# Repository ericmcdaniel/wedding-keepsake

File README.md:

# Wedding Keychain Keepsake

This is the full schematic, design, plans, and source code for the interactive RGB LED keepsake gadget from Eric and Stephie's wedding on Saturday August 15th 2026. These PCBs are attached to a keychain and were distributed to guests as keepsake party favors. The keychain displays a bright grid of LED lights and features simple animations and games.

# Modes

When powered on, the keychain begins in either one of two modes: Animation mode and Game mode. Press and Hold the button for one second to switch between Animation and Game modes.

### Animation Mode

The keychain displays an animation from the selection below. Single-press the button to cycle between the following animations.
* Tunnel
* Swipe
* Rainbow
* American Flag
* Candle

### Game Mode

As of this writing, the keychain only offers one game named *Dodge*. Dodge is a space-themed endless runner arcade survival game. You are piloting a space shuttle, traveling through the solar system. You encouter space debris, and must evade them before they collide into you.

Single-press the button to steer your rocket in the opposite direction to dodge obstacles. Survive as long as you can, even as you accelerate through the debris at progressively faster rates.

# Bill of Materials

* 32 acrylic-diffused RGB LEDs, arranged in an 8x4 matrix.
* ~~A MEMS microphone and op-amp for simple audio sampling (no FFT).~~
  * This idea was included in the design and was manufactured. The idea was to create additional audio-reactive (and interactive) modes like animations for decibel and music analyzers, but development time exceeded my delivery timeline. This will be revisited later in future updates.
* Animations can be cycled and games that can be played using the single tactile push button.
* Controlled by the AVR-based ATtiny1614 manufactured by *Microchip Technology*.
* Powered by a 24mm x 5mm CR2450 coin cell battery.
* On an 80mm x 30mm PCB with a D-hook clasp and snake keychain.
* Placed inside a custom-made sled enclosure with snap-fit sliding lid.

# Design

## 3D Rendering

<p align="center"><i>Front side of the PCB</i></p>

<p align="center"><i>Back side of the PCB</i></p>

## Electrical Schematic

## PCB Layout

<p align="center"><i>Layer 1 of the PCB (signals/components)</i></p>

<p align="center"><i>Layer 2 of the PCB (GND)</i><p>

<p align="center"><i>Layer 3 of the PCB (3V3 copper pour)</i><p>

<p align="center"><i>Layer 4 of the PCB (Additional signals/components)</i><p>

# Details

### Architecture and Engine

This repository was built using the toolkits provided by PlatformIO. It is based on the Arduino framework, though quite minimally. An RTOS is not used, fairly bare metal in terms of architecture. To keep things as efficient as possible, abstractions that Arduino provides like `digitalWrite()` were replaced with direct register manipulations, especially duirng hot execution paths. Most notably it is used during the LED rendering logic, which renders each row sequentially for 50 microseconds, creating a multiplexed effect on the display, as if all the LEDs were on simutaneously. The main reason that the Arduino framework is still used is because of the timers.

Internally, this repo was built on top of the custom game engine used in the [LumenLab](https://github.com/ericmcdaniel/lumenlab), with a handful of adaptations. This includes the platform-level core services, the engine, and general architecture from the LumenLab. This repo implements multiplexing manually, so libraries like FastLED used in the LumenLab could not be used. The keychain runs the main game loop at 60 Hz. Between each frame, the engine multiplexes each row at a frequency of 20 kHz (50 microseconds). Between each row rendering, three shift registers designated to the red, green, and blue channels take in a serial stream of bits to indicate if the respective color's LED should be on. If it's signal LOW, the LED turns on, and if signal HIGH then off. (this is in reverse because the MOSFETS are active HIGH).

Pulse-width modulation (PWM) is needed to dim the three primary colors, allowing for any arbitrary color can be made via blending. This was implemented using [bit-angle modulation (BAM)](https://www.desertember.com/posts/bit-angle-modulation.html) to determine the duty cycle. That was a headache, almost literally, because given large time values, the PWM's duty cycle would be so spread your eyes would noticably see the flicker. The color depth was reduced to 6-bit. The flicker isn't fully removed, but it's significantly better. Brightness and gamma correction was implemented, but disabled because adjustmenets is needed (again, mostly due to the noticable PWM flicker).

### Audio profiling (not implemented)

A MEMS microphone and amplifier was a part of the keychain's goal and is still a part of the design and schematic. The idea was realistic to implement, but was bound by an ambitious timeline, so I had to pause development that for now. The microphone still remains on the PCB since they were already manufactured (center-right). This gives me the opportunity to simply suspend working on the audio-reactive features rather than cancel entirely.

The idea for this keychain was to include audio reactivity, which would complement the already interactive animations. Running a full spectrum analyzer was not possible given the microcontroller selected, power constraints, and technical limitations like the inability to timely perform computationally heavy Fast-Fourier Transformations (FFT). So to be clear, it is too low-powered/low-budget to record conversation. Instead, the device was going to sample decibel levels in real time and display a sound-reactive bar, like the EQ on a stereo system. Another idea I had for the built-in microphone was to make the devices react to the wedding reception music live in real time. Between songs, I could have my computer play a swift, 20+ kHz logic signal at the before every song. This high-frequency chirp wouldn't be heard by humans, but detected by this keychain. It would then decode the message, and play an animation or color theme dynamically, as if it's listening to the music and dancing along.

These were two ideas that have artifacts on the board, but were not implemented.

# Development

### Software

The keychain is programmable using the UPDI protocol, which is the newer version of AVR's ISP and JTAG programming. The UPDI (PA0, pin 10) is exposed on a THT test pad, along with 3V3 and GND. To program the device, you need a $7 module called the UPDI Friend - USB Serial UPDI Programmer from [Adafruit](https://www.adafruit.com/product/5879) or [Digikey](https://www.digikey.com/en/products/detail/adafruit-industries-llc/5879/22596413). Releases are provided every PR and can be flashed directly. I'll write instructions to directly flash the device later (hopefully), and possibly even dockerize it for simplicity. Until then, the easiest way to update is to install the PlatformIO toolkit, compile this repo locally, and flash using the *PlatformIO: Upload (Release)* build script included.

In addition to the UPDI pin, PB2 (pin 7) and PB3 (pin 6) are mapped to TX and RX respectively. Because they were unused, these pins are exposed as SMD test pads. This allows you to probe TX (PB2) to read the serial logs, if you compiled the debug version.

### Hardware

The PCB design files were made using KiCad 9.0.5. The board layout was optimized for the manufacturing capabilities of [PCBWay](https://www.pcbway.com/). Before you start writing me hate mail, know that I'm aware of the issues, such as the lack of ESD protection and reverse polarity protection. Perhaps a future revision can include these, but I have no such plans.

The enclosure was made using FreeCAD 1.1.0. They also suck, but I tried. The models were also exported as .3mf files, and were optimized for immediate FDM printing, particularly the Bambu Labs A1 Combo. Feel free to adjust as needed for your machine. The model includes a sled enclosure which retains the PCB using four friction fit ribs. A lid is attached by sliding it along the guide rails from left to right. A snap-fit latch locks the lid in place, preventing it from falling off. I printed this using Bambu Lab's PLA Basic, however given the variance between 3D printers, brands, filament, and other conditions, your mileage may vary.

## AI Disclaimer

AI was consulted as a research and discovery analysis tool. I asked it general design, architecture, and best practices questions, especially during the board bring-up stage. I don't have a professional background in electrical engineering (is YouTube University accredited?), so I used it as a an informational resource. 

*Generative* AI, however, was **not** used to author code. Call me a luddite, but this is out of priniciple. Software engineering is an art as it is a science. Cheers to all the other crazies out there!

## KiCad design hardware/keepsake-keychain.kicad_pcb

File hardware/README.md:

# Enclosure

<p align="center"><i>Enclosure Sled without the Lid</i></p>

<p align="center"><i>Enclosure with the Lid</i></p>

# PCB 3D Rendering

<p align="center"><i>Front side of the PCB</i></p>

<p align="center"><i>Back side of the PCB</i></p>

# Electrical Schematic

# PCB Layout

<p align="center"><i>Layer 1 of the PCB (signals/components)</i></p>

<p align="center"><i>Layer 2 of the PCB (GND)</i><p>

<p align="center"><i>Layer 3 of the PCB (3V3 copper pour)</i><p>

<p align="center"><i>Layer 4 of the PCB (Additional signals/components)</i><p>

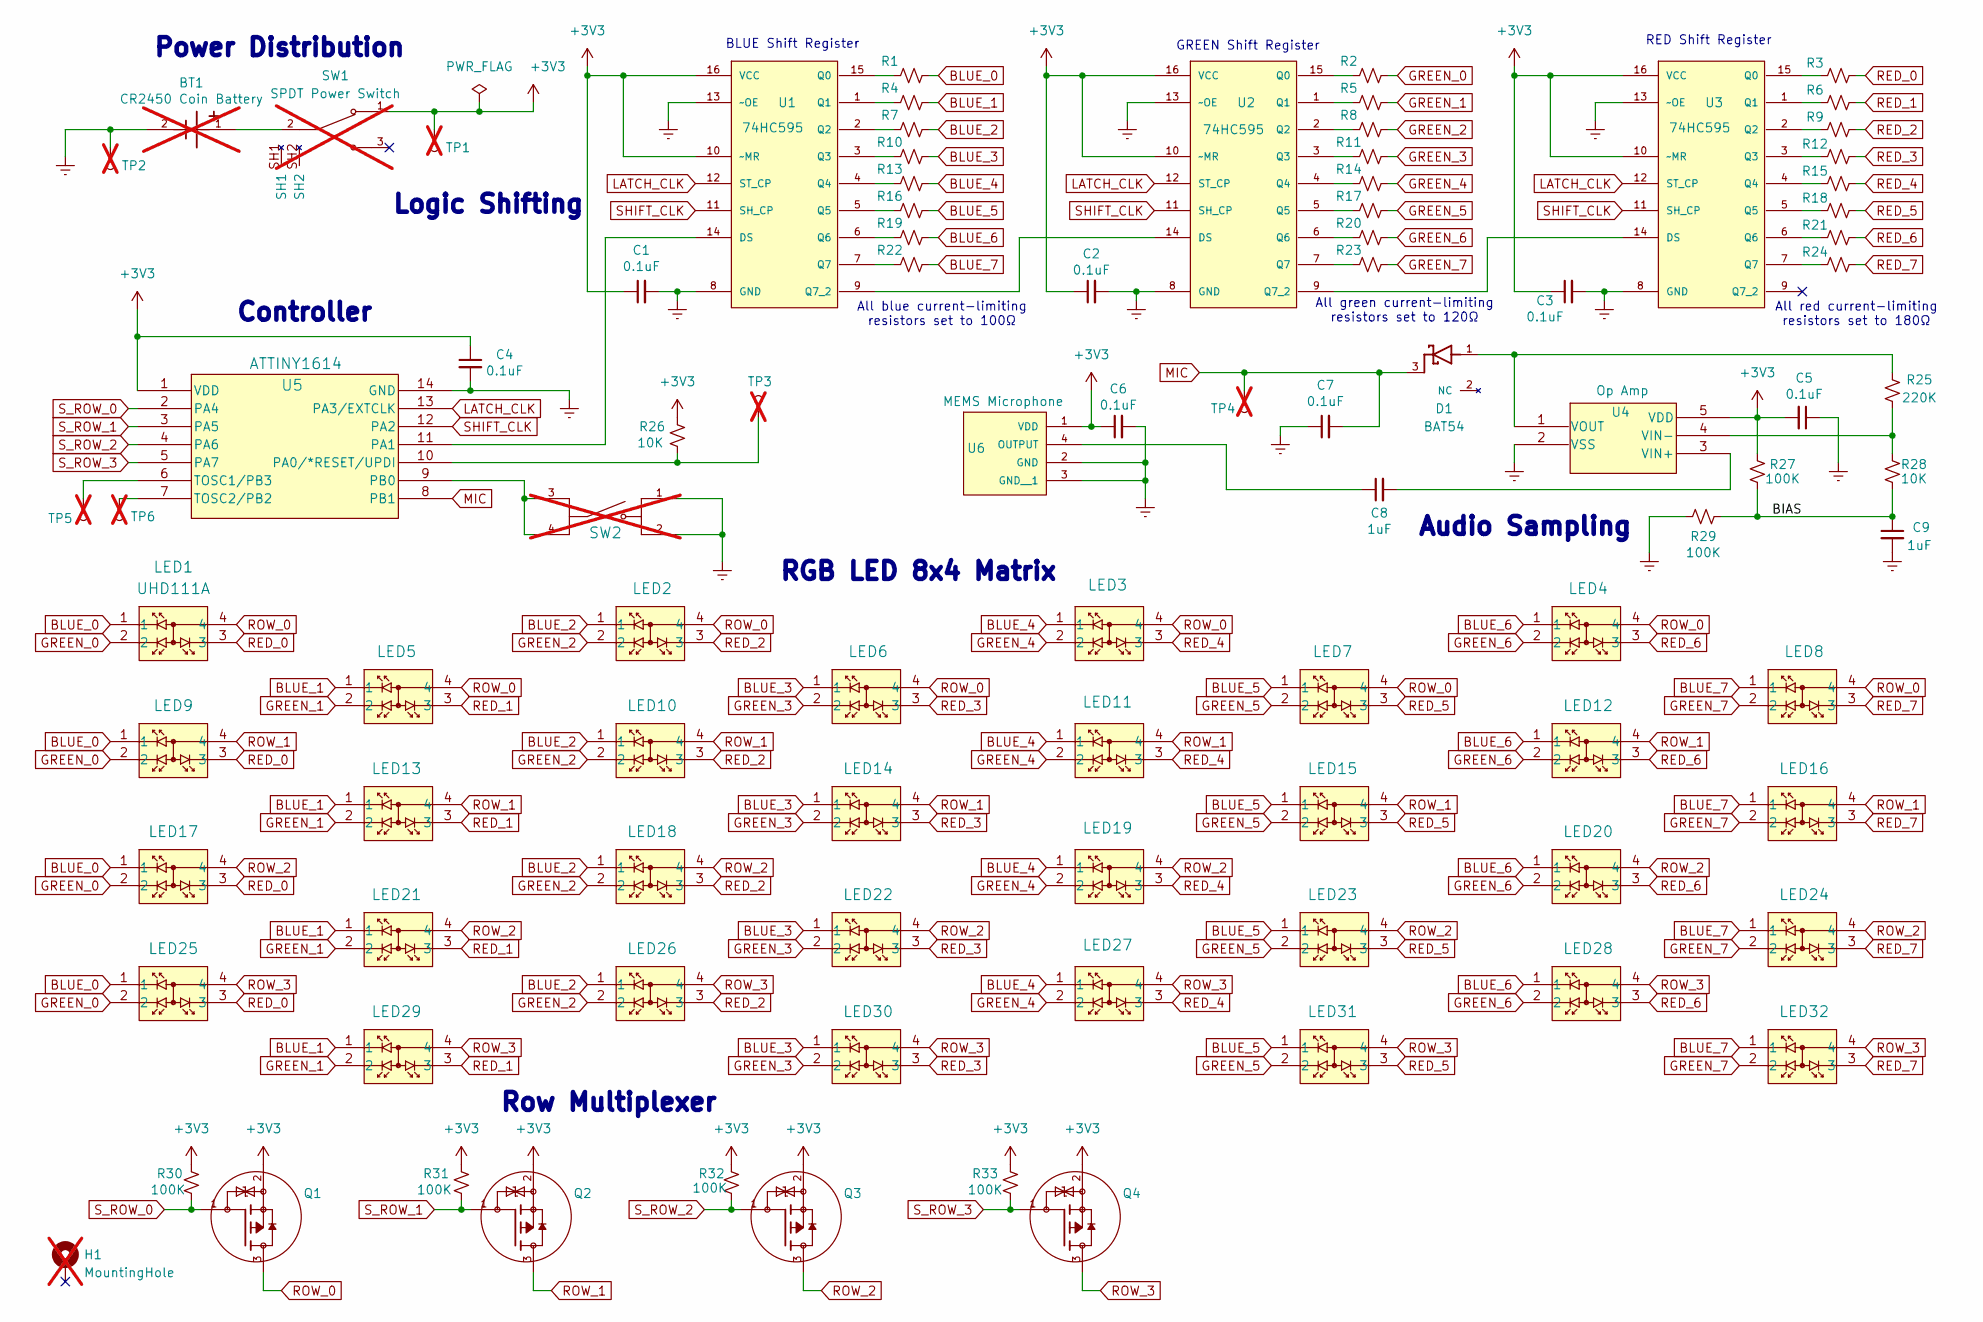
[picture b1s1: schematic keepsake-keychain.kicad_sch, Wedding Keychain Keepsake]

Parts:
BT1: CR2450 Coin Battery; battery-holder; PARTREV H; Digi-Key_PN BHX1-2450-SM-ND; not fitted
C1, C2, C3, C4, C5, C6, C7: 0.1uF; C_0603_1608Metric_Pad1.08x0.95mm_HandSolder; MPN GMC10X7R104K25NT; Digi-Key_PN 4713-GMC10X7R104K25NTCT-ND
C8, C9: 1uF; C_0603_1608Metric_Pad1.08x0.95mm_HandSolder; MPN 0603B105K250CT; Digi-Key_PN 1292-0603B105K250CT-ND
D1: BAT54; SOT95P240X120-3N; PARTREV 2025-04-24; Digi-Key_PN 4878-BAT54CT-ND
H1: MountingHole; MountingHole_3.5mm_Pad_TopBottom; not fitted
LED1, LED2, LED3, LED4, LED5, LED6, LED7, LED8, LED9, LED10, LED11, LED12, LED13, LED14, LED15, LED16, LED17, LED18, LED19, LED20, LED21, LED22, LED23, LED24, LED25, LED26, LED27, LED28, LED29, LED30, LED31, LED32: UHD111A; rgb-led; MPN UHD111A-FKA-C3K23E1L3VG5ZB3Z3; Digi-Key_PN 90-UHD111A-FKA-C3K23E1L3VG5ZB3Z3-ND
Q1, Q2, Q3, Q4: MMFTP4042K; mosfet; PARTREV 2024-05-07; Digi-Key_PN 4878-MMFTP4042KCT-ND
R1, R4, R7, R10, R13, R16, R19, R22: 100; R_0603_1608Metric_Pad0.98x0.95mm_HandSolder; MPN WR06X101 JTL; Digi-Key_PN 1292-WR06X101JTLCT-ND
R2, R5, R8, R11, R14, R17, R20, R23: 120; R_0603_1608Metric_Pad0.98x0.95mm_HandSolder; MPN RMCF0603JT120R; Digi-Key_PN RMCF0603JT120RCT-ND
R3, R6, R9, R12, R15, R18, R21, R24: 180; R_0603_1608Metric_Pad0.98x0.95mm_HandSolder; MPN RMCF0603JT180R; Digi-Key_PN RMCF0603JT180RCT-ND
R25: 220K; R_0603_1608Metric_Pad0.98x0.95mm_HandSolder; MPN WR06X2203FTL; Digi-Key_PN 1292-WR06X2203FTLCT-ND
R26, R28: 10K; R_0603_1608Metric_Pad0.98x0.95mm_HandSolder; MPN RC0603FR-0710KL; Digi-Key_PN 311-10.0KHRCT-ND
R27, R29, R30, R31, R32, R33: 100K; R_0603_1608Metric_Pad0.98x0.95mm_HandSolder; MPN CR0603-JW-104ELF; Digi-Key_PN CR0603-JW-104ELFCT-ND
SW1: SPDT Power Switch; spdt-switch; PARTREV 1.01; Digi-Key_PN 2223-SLW-835636-3A-RA-N-D-ND; not fitted
SW2: PTS636 SK25J SMTR LFS; SW_TS18-5-15-SL-160-SMT-TR; PARTREV 1.02; Digi-Key_PN 2223-TS18-5-15-SL-160-SMT-TRCT-ND; not fitted
TP1, TP3: 5002; TestPoint_THTPad_D2.0mm_Drill1.0mm; not fitted
TP2: 5002; TestPoint_THTPad_2.0x2.0mm_Drill1.0mm; not fitted
TP4, TP5, TP6: 5002; TestPoint_Pad_D1.0mm; not fitted
U1, U2, U3: 74HC595; shift-register; MPN 74HC595PW,118; Digi-Key_PN 1727-3068-1-ND
U4: Op Amp; SOT-23-5_MC_MCH; MPN MCP6001T-I/OT; Digi-Key_PN MCP6001T-I/OTCT-ND
U5: ATTINY1614; SOIC14_SL_MCH; MPN ATTINY1614-SSF; Digi-Key_PN ATTINY1614-SSF-ND
U6: MEMS Microphone; MIC_3SM123C4T1QA; PARTREV 1.4; Digi-Key_PN 5280-3SM123C4T1QACT-ND

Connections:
+3V3: C1.1, C2.1, C3.1, C4.1, C5.2, C6.1, Q1.2, Q2.2, Q3.2, Q4.2, R26.2, R27.1, R30.2, R31.2, R32.2, R33.2, SW1.1, TP1.1, U1.10 (~MR), U1.16 (VCC), U2.10 (~MR), U2.16 (VCC), U3.10 (~MR), U3.16 (VCC), U4.5 (VDD), U5.1 (VDD), U6.1 (VDD)
/BIAS: C9.1, R27.2, R28.2, R29.1
BLUE_0: LED1.1, LED9.1, LED17.1, LED25.1, R1.1
BLUE_1: LED5.1, LED13.1, LED21.1, LED29.1, R4.1
BLUE_2: LED2.1, LED10.1, LED18.1, LED26.1, R7.1
BLUE_3: LED6.1, LED14.1, LED22.1, LED30.1, R10.1
BLUE_4: LED3.1, LED11.1, LED19.1, LED27.1, R13.1
BLUE_5: LED7.1, LED15.1, LED23.1, LED31.1, R16.1
BLUE_6: LED4.1, LED12.1, LED20.1, LED28.1, R19.1
BLUE_7: LED8.1, LED16.1, LED24.1, LED32.1, R22.1
GND: BT1.2, C1.2, C2.2, C3.2, C4.2, C5.1, C6.2, C7.1, C9.2, R29.2, SW2.1, SW2.2, TP2.1, U1.8 (GND), U1.13 (~OE), U2.8 (GND), U2.13 (~OE), U3.8 (GND), U3.13 (~OE), U4.2 (VSS), U5.14 (GND), U6.2 (GND), U6.3 (GND__1)
GREEN_0: LED1.2, LED9.2, LED17.2, LED25.2, R2.1
GREEN_1: LED5.2, LED13.2, LED21.2, LED29.2, R5.1
GREEN_2: LED2.2, LED10.2, LED18.2, LED26.2, R8.1
GREEN_3: LED6.2, LED14.2, LED22.2, LED30.2, R11.1
GREEN_4: LED3.2, LED11.2, LED19.2, LED27.2, R14.1
GREEN_5: LED7.2, LED15.2, LED23.2, LED31.2, R17.1
GREEN_6: LED4.2, LED12.2, LED20.2, LED28.2, R20.1
GREEN_7: LED8.2, LED16.2, LED24.2, LED32.2, R23.1
LATCH_CLK: U1.12 (ST_CP), U2.12 (ST_CP), U3.12 (ST_CP), U5.13 (PA3/EXTCLK)
MIC: C7.2, D1.3, TP4.1, U5.8 (PB1)
unnamed: BT1.1, SW1.2
unnamed: U1.14 (DS), U5.11 (PA1)
unnamed: R1.2, U1.15 (Q0)
unnamed: R4.2, U1.1 (Q1)
unnamed: R7.2, U1.2 (Q2)
unnamed: R10.2, U1.3 (Q3)
unnamed: R13.2, U1.4 (Q4)
unnamed: R16.2, U1.5 (Q5)
unnamed: R19.2, U1.6 (Q6)
unnamed: R22.2, U1.7 (Q7)
unnamed: U1.9 (Q7_2), U2.14 (DS)
unnamed: R2.2, U2.15 (Q0)
unnamed: R5.2, U2.1 (Q1)
unnamed: R8.2, U2.2 (Q2)
unnamed: R11.2, U2.3 (Q3)
unnamed: R14.2, U2.4 (Q4)
unnamed: R17.2, U2.5 (Q5)
unnamed: R20.2, U2.6 (Q6)
unnamed: R23.2, U2.7 (Q7)
unnamed: U2.9 (Q7_2), U3.14 (DS)
unnamed: R3.2, U3.15 (Q0)
unnamed: R6.2, U3.1 (Q1)
unnamed: R9.2, U3.2 (Q2)
unnamed: R12.2, U3.3 (Q3)
unnamed: R15.2, U3.4 (Q4)
unnamed: R18.2, U3.5 (Q5)
unnamed: R21.2, U3.6 (Q6)
unnamed: R24.2, U3.7 (Q7)
unnamed: C8.2, U4.3 (VIN+)
unnamed: R25.2, R28.1, U4.4 (VIN-)
unnamed: D1.1, R25.1, U4.1 (VOUT)
unnamed: R26.1, TP3.1, U5.10 (PA0/*RESET/UPDI)
unnamed: SW2.3, SW2.4, U5.9 (PB0)
unnamed: TP5.1, U5.6 (TOSC1/PB3)
unnamed: TP6.1, U5.7 (TOSC2/PB2)
unnamed: C8.1, U6.4 (OUTPUT)
RED_0: LED1.3, LED9.3, LED17.3, LED25.3, R3.1
RED_1: LED5.3, LED13.3, LED21.3, LED29.3, R6.1
RED_2: LED2.3, LED10.3, LED18.3, LED26.3, R9.1
RED_3: LED6.3, LED14.3, LED22.3, LED30.3, R12.1
RED_4: LED3.3, LED11.3, LED19.3, LED27.3, R15.1
RED_5: LED7.3, LED15.3, LED23.3, LED31.3, R18.1
RED_6: LED4.3, LED12.3, LED20.3, LED28.3, R21.1
RED_7: LED8.3, LED16.3, LED24.3, LED32.3, R24.1
ROW_0: LED1.4, LED2.4, LED3.4, LED4.4, LED5.4, LED6.4, LED7.4, LED8.4, Q1.3
ROW_1: LED9.4, LED10.4, LED11.4, LED12.4, LED13.4, LED14.4, LED15.4, LED16.4, Q2.3
ROW_2: LED17.4, LED18.4, LED19.4, LED20.4, LED21.4, LED22.4, LED23.4, LED24.4, Q3.3
ROW_3: LED25.4, LED26.4, LED27.4, LED28.4, LED29.4, LED30.4, LED31.4, LED32.4, Q4.3
SHIFT_CLK: U1.11 (SH_CP), U2.11 (SH_CP), U3.11 (SH_CP), U5.12 (PA2)
S_ROW_0: Q1.1, R30.1, U5.2 (PA4)
S_ROW_1: Q2.1, R31.1, U5.3 (PA5)
S_ROW_2: Q3.1, R32.1, U5.4 (PA6)
S_ROW_3: Q4.1, R33.1, U5.5 (PA7)

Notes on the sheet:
All red current-limiting resistors set to 180Ω
All blue current-limiting resistors set to 100Ω
BLUE Shift Register
RED Shift Register
Power Distribution
All green current-limiting resistors set to 120Ω
RGB LED 8x4 Matrix
Controller
Row Multiplexer
Logic Shifting
Audio Sampling
GREEN Shift Register

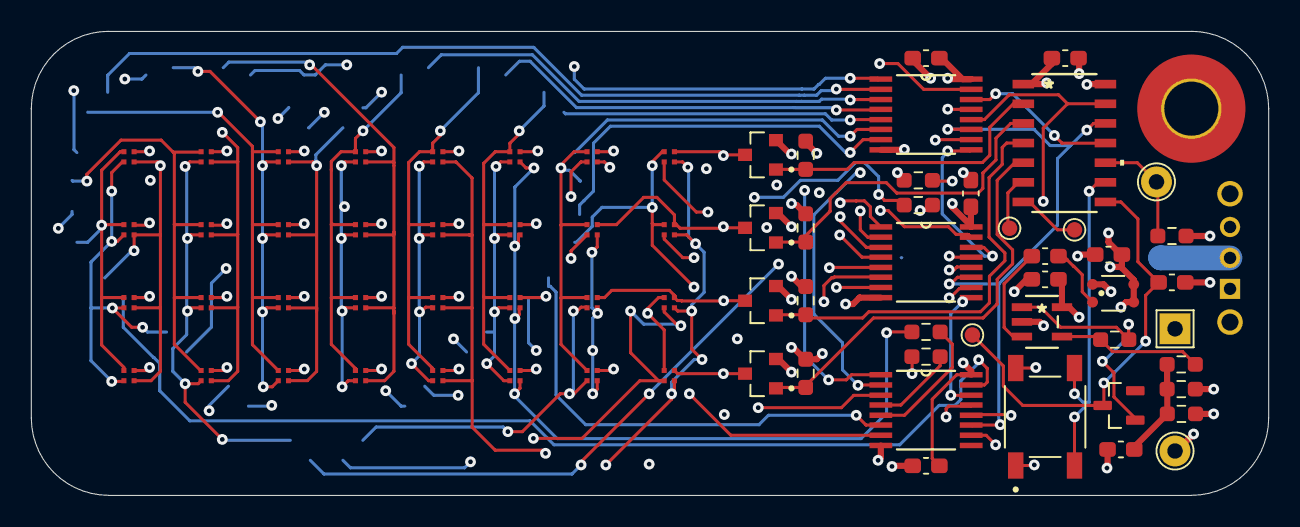
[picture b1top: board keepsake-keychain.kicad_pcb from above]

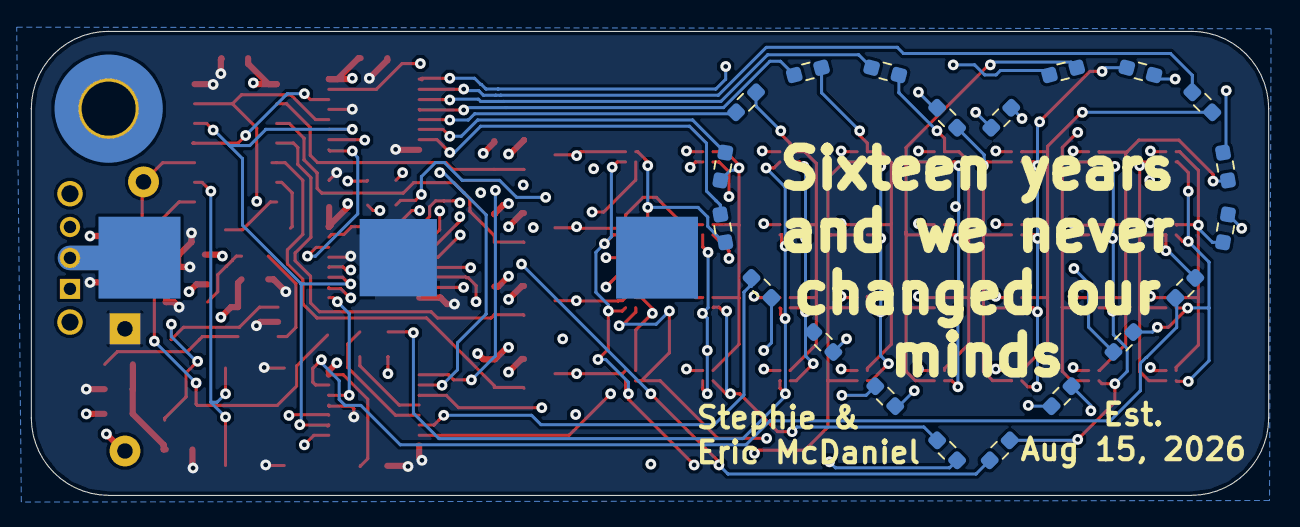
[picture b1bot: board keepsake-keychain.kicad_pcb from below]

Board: 4 copper layers, 80.0 x 30.0 mm, 95 parts (21 on the bottom side), 74 nets.

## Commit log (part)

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2026-06-06 Add CR 2032 coin battery holder
2026-06-06 Add SPDT switch
2026-06-06 Add RGB LED
2026-06-06 Add 74HC595 shift register to lib
2026-06-06 Add ATtiny1614 IC
2026-06-06 Restructure component library
2026-06-06 Add P-channel MOSFET
2026-06-08 Add pin for UPDI programming
2026-06-08 Add tactile push button
2026-06-08 Connect MOSFETs, add MEMS microphone
2026-06-09 Add op-amp
2026-06-09 Add filtering and label nets
2026-06-09 Continue schematic stweaks, connect nets
2026-06-10 Replace tactile button and power switch for space conservancy
2026-06-10 Upgrade CR2032 to CR2450 for longer battery life
2026-06-10 Assign footprints to components
2026-06-10 Swap push button and slide switch for better options
2026-06-11 Attach models. Complete schematic, pass ERC.
2026-06-11 Place LED passives in line
2026-06-12 Rename nets, move resistors to rear
2026-06-12 Finish heart, refine references designator positions
2026-06-13 Fix broken net, fix via annular ring constraint
2026-06-13 Place remaining passives
2026-06-14 Fix errors from unassigned pins
2026-06-14 Replace tactile push button for stable, lower profile
2026-06-14 Route all traces for controller
2026-06-14 Route first half of LED traces
2026-06-15 Convert to four-layer board (sigh)
2026-06-16 Finish routing traces, export BOM and images
2026-06-16 Clean BOM, export gerbers
2026-06-17 Tweak layout for additional GND pour
2026-06-18 Final export, release for pcbway
2026-06-22 Scaffold project structure
2026-06-24 Begin engine/core build, forked from LumenLab
2026-06-29 Configure firmware flashing va UPDI
